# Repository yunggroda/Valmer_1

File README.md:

# Valmer_1

Custom split ergonomic keyboard project.

## Structure
- ergogen/ – layout and generation
- kicad/ – PCB design
- firmware/ – firmware (TBD)
- case/ – 3D printed parts
- docs/ – notes and decisions

## Status
Early development

## Goals
- Split keyboard
- RP2040 (Pro Micro)
- Ergogen-based workflow

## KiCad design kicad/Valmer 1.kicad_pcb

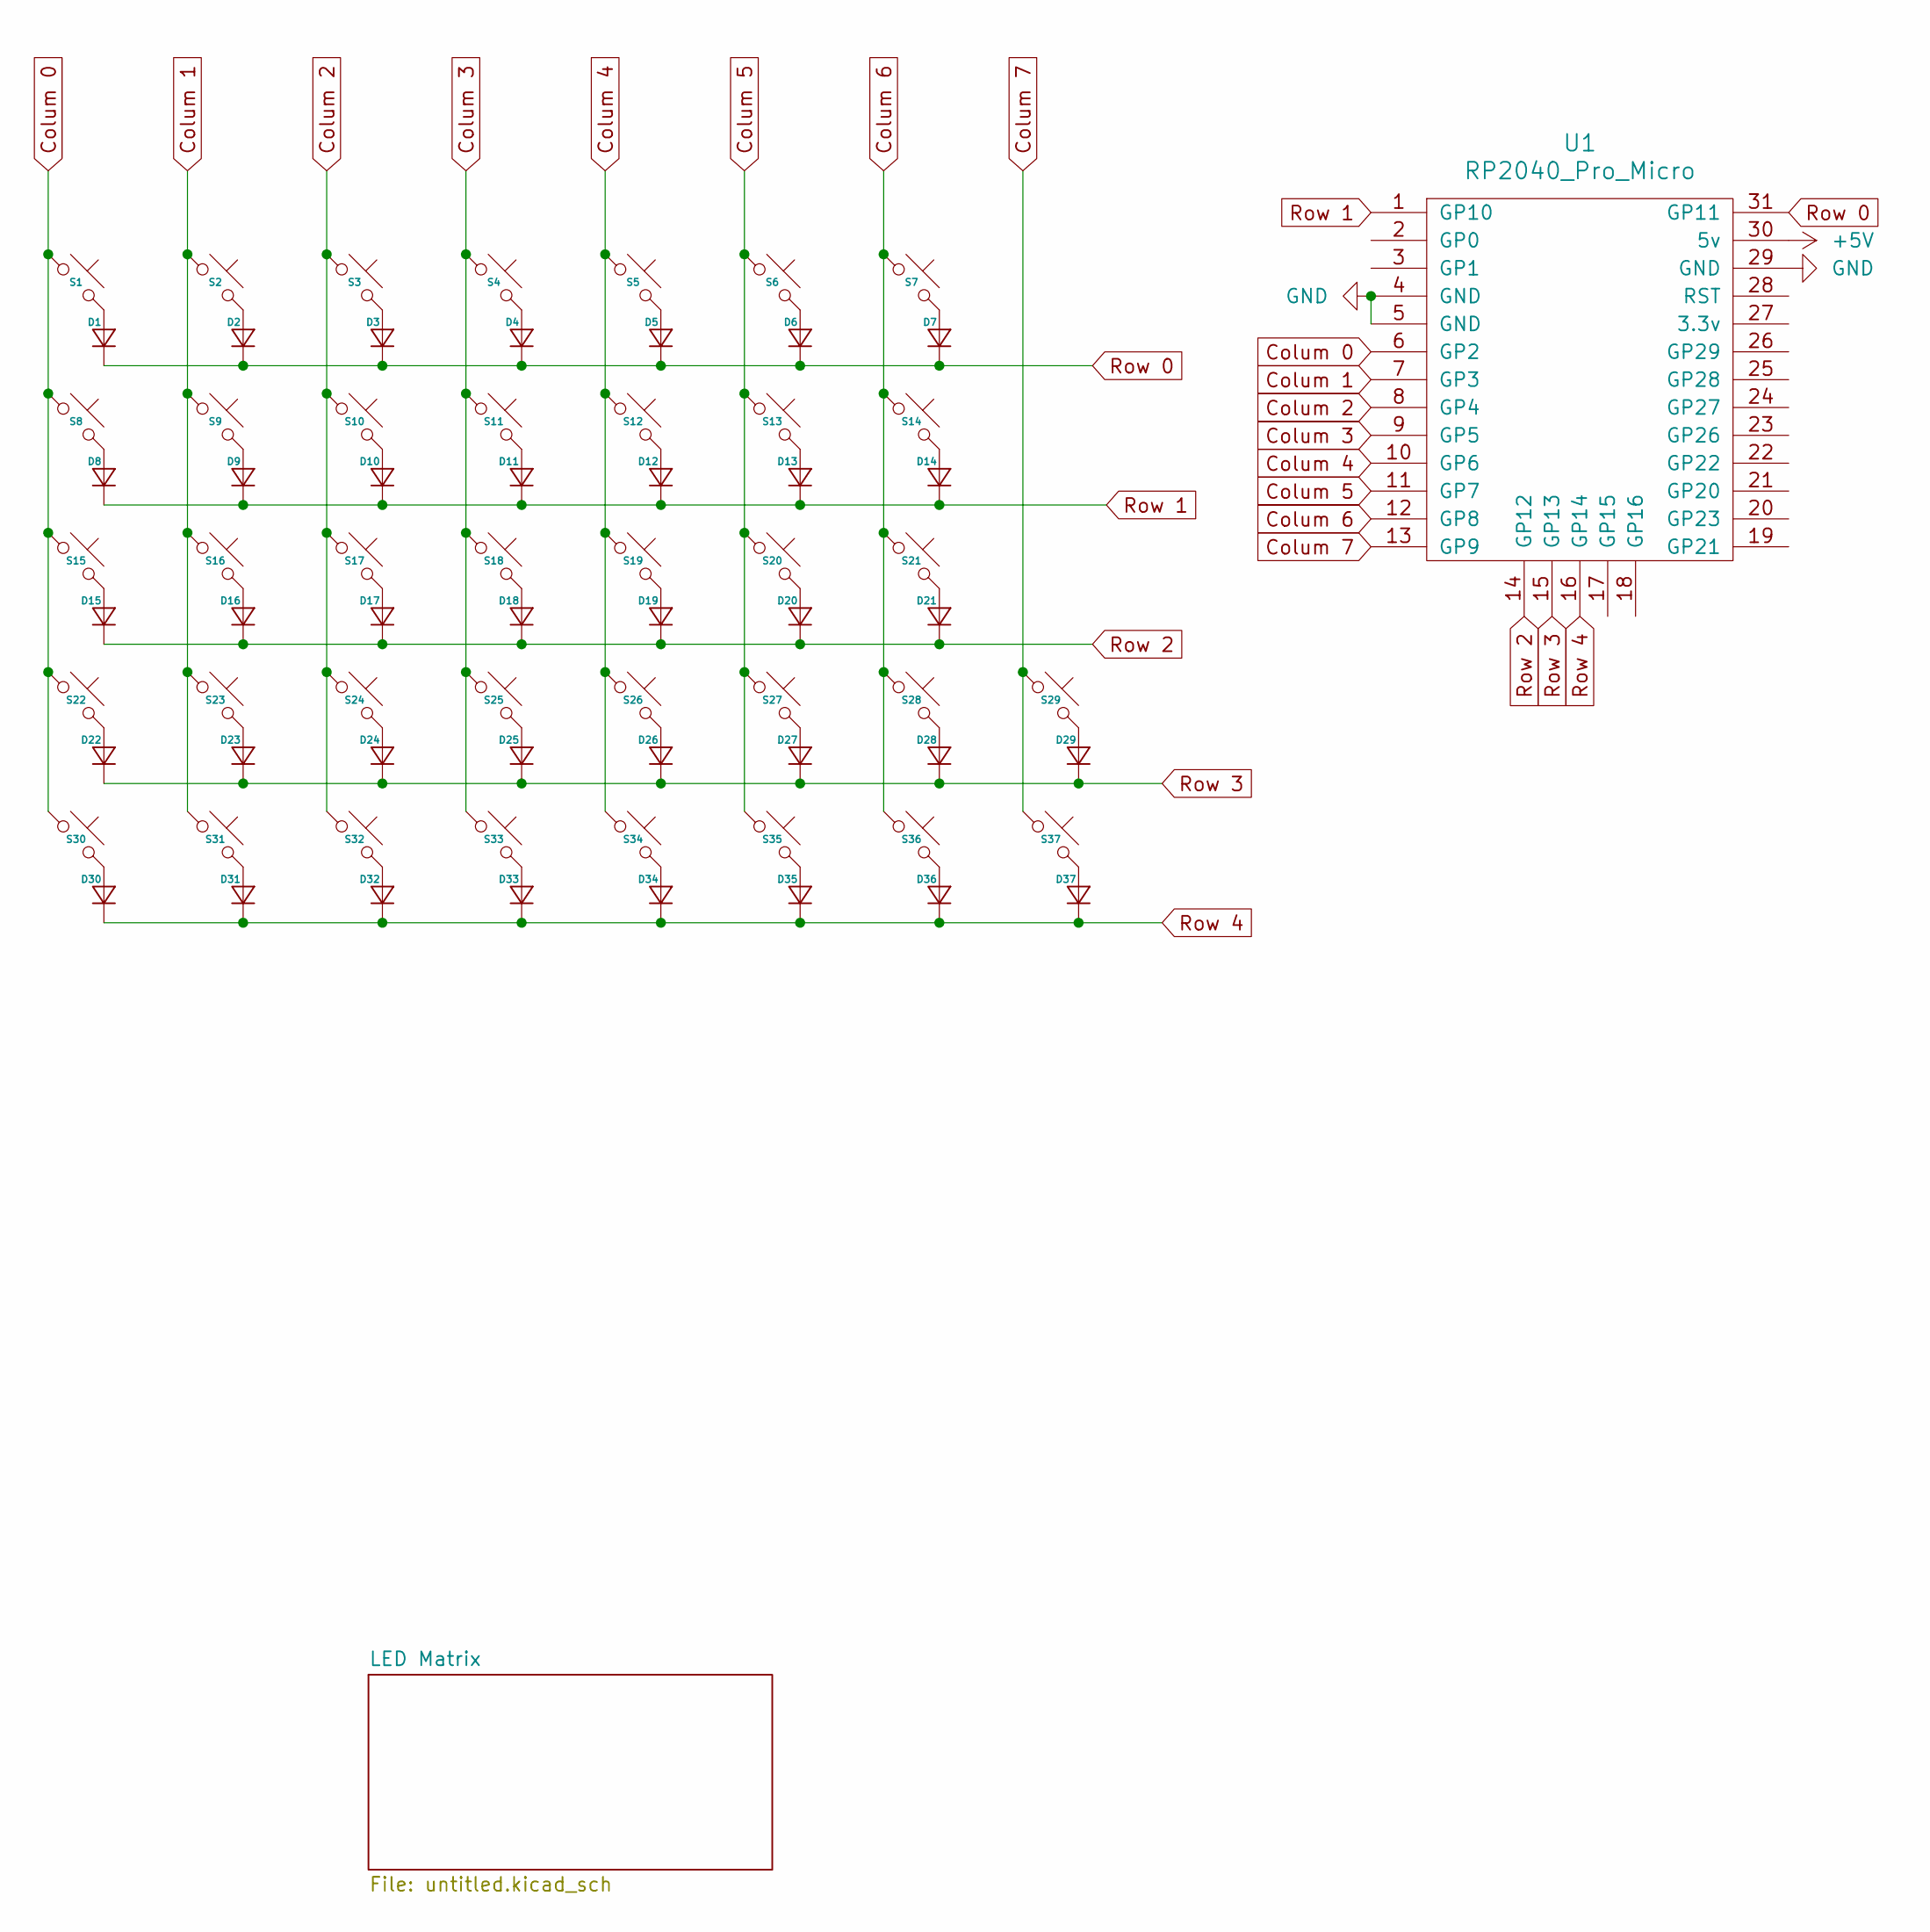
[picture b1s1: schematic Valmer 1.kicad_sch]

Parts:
D1, D2, D3, D4, D5, D6, D7, D8, D9, D10, D11, D12, D13, D14, D15, D16, D17, D18, D19, D20, D21, D22, D23, D24, D25, D26, D27, D28, D29, D30, D31, D32, D33, D34, D35, D36, D37: Diode_SOD-123
S1, S2, S3, S4, S5, S6, S7, S8, S9, S10, S11, S12, S13, S14, S15, S16, S17, S18, S19, S20, S21, S22, S23, S24, S25, S26, S27, S28, S29, S30, S31, S32, S33, S34, S35, S36, S37: Hotswap_Choc_V1V2_1.00u
U1: RP2040_Pro_Micro

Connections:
+5V: U1.30 (5v); also elsewhere on the board
Colum 0: S1.1, S8.1, S15.1, S22.1, S30.1, U1.6 (GP2)
Colum 1: S2.1, S9.1, S16.1, S23.1, S31.1, U1.7 (GP3)
Colum 2: S3.1, S10.1, S17.1, S24.1, S32.1, U1.8 (GP4)
Colum 3: S4.1, S11.1, S18.1, S25.1, S33.1, U1.9 (GP5)
Colum 4: S5.1, S12.1, S19.1, S26.1, S34.1, U1.10 (GP6)
Colum 5: S6.1, S13.1, S20.1, S27.1, S35.1, U1.11 (GP7)
Colum 6: S7.1, S14.1, S21.1, S28.1, S36.1, U1.12 (GP8)
Colum 7: S29.1, S37.1, U1.13 (GP9)
GND: U1.4 (GND), U1.5 (GND), U1.29 (GND); also elsewhere on the board
unnamed: D1.2 (A), S1.2
unnamed: D2.2 (A), S2.2
unnamed: D3.2 (A), S3.2
unnamed: D4.2 (A), S4.2
unnamed: D5.2 (A), S5.2
unnamed: D6.2 (A), S6.2
unnamed: D7.2 (A), S7.2
unnamed: D8.2 (A), S8.2
unnamed: D9.2 (A), S9.2
unnamed: D10.2 (A), S10.2
unnamed: D11.2 (A), S11.2
unnamed: D12.2 (A), S12.2
unnamed: D13.2 (A), S13.2
unnamed: D14.2 (A), S14.2
unnamed: D15.2 (A), S15.2
unnamed: D16.2 (A), S16.2
unnamed: D17.2 (A), S17.2
unnamed: D18.2 (A), S18.2
unnamed: D19.2 (A), S19.2
unnamed: D20.2 (A), S20.2
unnamed: D21.2 (A), S21.2
unnamed: D22.2 (A), S22.2
unnamed: D23.2 (A), S23.2
unnamed: D24.2 (A), S24.2
unnamed: D25.2 (A), S25.2
unnamed: D26.2 (A), S26.2
unnamed: D27.2 (A), S27.2
unnamed: D28.2 (A), S28.2
unnamed: D29.2 (A), S29.2
unnamed: D30.2 (A), S30.2
unnamed: D31.2 (A), S31.2
unnamed: D32.2 (A), S32.2
unnamed: D33.2 (A), S33.2
unnamed: D34.2 (A), S34.2
unnamed: D35.2 (A), S35.2
unnamed: D36.2 (A), S36.2
unnamed: D37.2 (A), S37.2
Row 0: D1.1 (K), D2.1 (K), D3.1 (K), D4.1 (K), D5.1 (K), D6.1 (K), D7.1 (K), U1.31 (GP11)
Row 1: D8.1 (K), D9.1 (K), D10.1 (K), D11.1 (K), D12.1 (K), D13.1 (K), D14.1 (K), U1.1 (GP10)
Row 2: D15.1 (K), D16.1 (K), D17.1 (K), D18.1 (K), D19.1 (K), D20.1 (K), D21.1 (K), U1.14 (GP12)
Row 3: D22.1 (K), D23.1 (K), D24.1 (K), D25.1 (K), D26.1 (K), D27.1 (K), D28.1 (K), D29.1 (K), U1.15 (GP13)
Row 4: D30.1 (K), D31.1 (K), D32.1 (K), D33.1 (K), D34.1 (K), D35.1 (K), D36.1 (K), D37.1 (K), U1.16 (GP14)

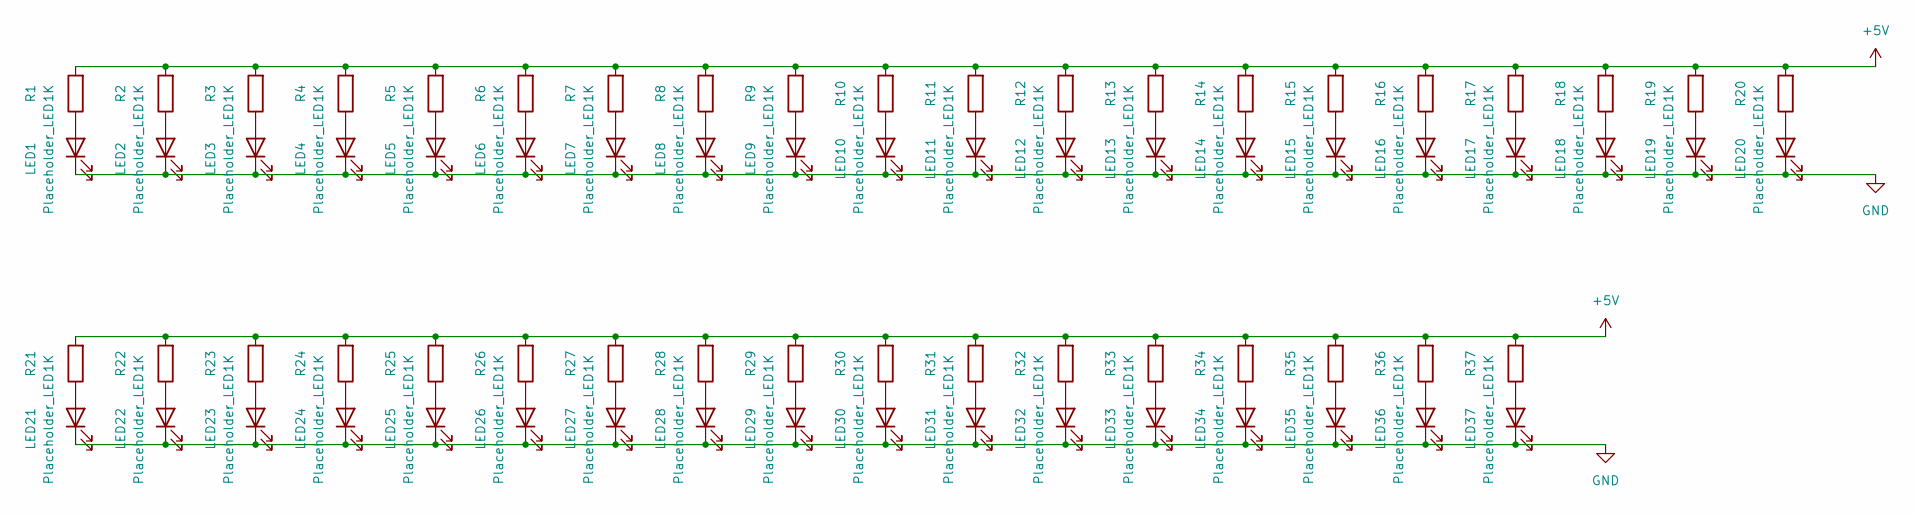
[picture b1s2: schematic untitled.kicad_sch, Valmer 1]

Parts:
LED1, LED2, LED3, LED4, LED5, LED6, LED7, LED8, LED9, LED10, LED11, LED12, LED13, LED14, LED15, LED16, LED17, LED18, LED19, LED20, LED21, LED22, LED23, LED24, LED25, LED26, LED27, LED28, LED29, LED30, LED31, LED32, LED33, LED34, LED35, LED36, LED37: Placeholder_LED; LED_0603_1608Metric
R1, R2, R3, R4, R5, R6, R7, R8, R9, R10, R11, R12, R13, R14, R15, R16, R17, R18, R19, R20, R21, R22, R23, R24, R25, R26, R27, R28, R29, R30, R31, R32, R33, R34, R35, R36, R37: 1K; R_0603_1608Metric

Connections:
+5V: R1.2, R2.2, R3.2, R4.2, R5.2, R6.2, R7.2, R8.2, R9.2, R10.2, R11.2, R12.2, R13.2, R14.2, R15.2, R16.2, R17.2, R18.2, R19.2, R20.2, R21.2, R22.2, R23.2, R24.2, R25.2, R26.2, R27.2, R28.2, R29.2, R30.2, R31.2, R32.2, R33.2, R34.2, R35.2, R36.2, R37.2; also elsewhere on the board
GND: LED1.1 (K), LED2.1 (K), LED3.1 (K), LED4.1 (K), LED5.1 (K), LED6.1 (K), LED7.1 (K), LED8.1 (K), LED9.1 (K), LED10.1 (K), LED11.1 (K), LED12.1 (K), LED13.1 (K), LED14.1 (K), LED15.1 (K), LED16.1 (K), LED17.1 (K), LED18.1 (K), LED19.1 (K), LED20.1 (K), LED21.1 (K), LED22.1 (K), LED23.1 (K), LED24.1 (K), LED25.1 (K), LED26.1 (K), LED27.1 (K), LED28.1 (K), LED29.1 (K), LED30.1 (K), LED31.1 (K), LED32.1 (K), LED33.1 (K), LED34.1 (K), LED35.1 (K), LED36.1 (K), LED37.1 (K); also elsewhere on the board
unnamed: LED1.2 (A), R1.1
unnamed: LED2.2 (A), R2.1
unnamed: LED3.2 (A), R3.1
unnamed: LED4.2 (A), R4.1
unnamed: LED5.2 (A), R5.1
unnamed: LED6.2 (A), R6.1
unnamed: LED7.2 (A), R7.1
unnamed: LED8.2 (A), R8.1
unnamed: LED9.2 (A), R9.1
unnamed: LED10.2 (A), R10.1
unnamed: LED11.2 (A), R11.1
unnamed: LED12.2 (A), R12.1
unnamed: LED13.2 (A), R13.1
unnamed: LED14.2 (A), R14.1
unnamed: LED15.2 (A), R15.1
unnamed: LED16.2 (A), R16.1
unnamed: LED17.2 (A), R17.1
unnamed: LED18.2 (A), R18.1
unnamed: LED19.2 (A), R19.1
unnamed: LED20.2 (A), R20.1
unnamed: LED21.2 (A), R21.1
unnamed: LED22.2 (A), R22.1
unnamed: LED23.2 (A), R23.1
unnamed: LED24.2 (A), R24.1
unnamed: LED25.2 (A), R25.1
unnamed: LED26.2 (A), R26.1
unnamed: LED27.2 (A), R27.1
unnamed: LED28.2 (A), R28.1
unnamed: LED29.2 (A), R29.1
unnamed: LED30.2 (A), R30.1
unnamed: LED31.2 (A), R31.1
unnamed: LED32.2 (A), R32.1
unnamed: LED33.2 (A), R33.1
unnamed: LED34.2 (A), R34.1
unnamed: LED35.2 (A), R35.1
unnamed: LED36.2 (A), R36.1
unnamed: LED37.2 (A), R37.1

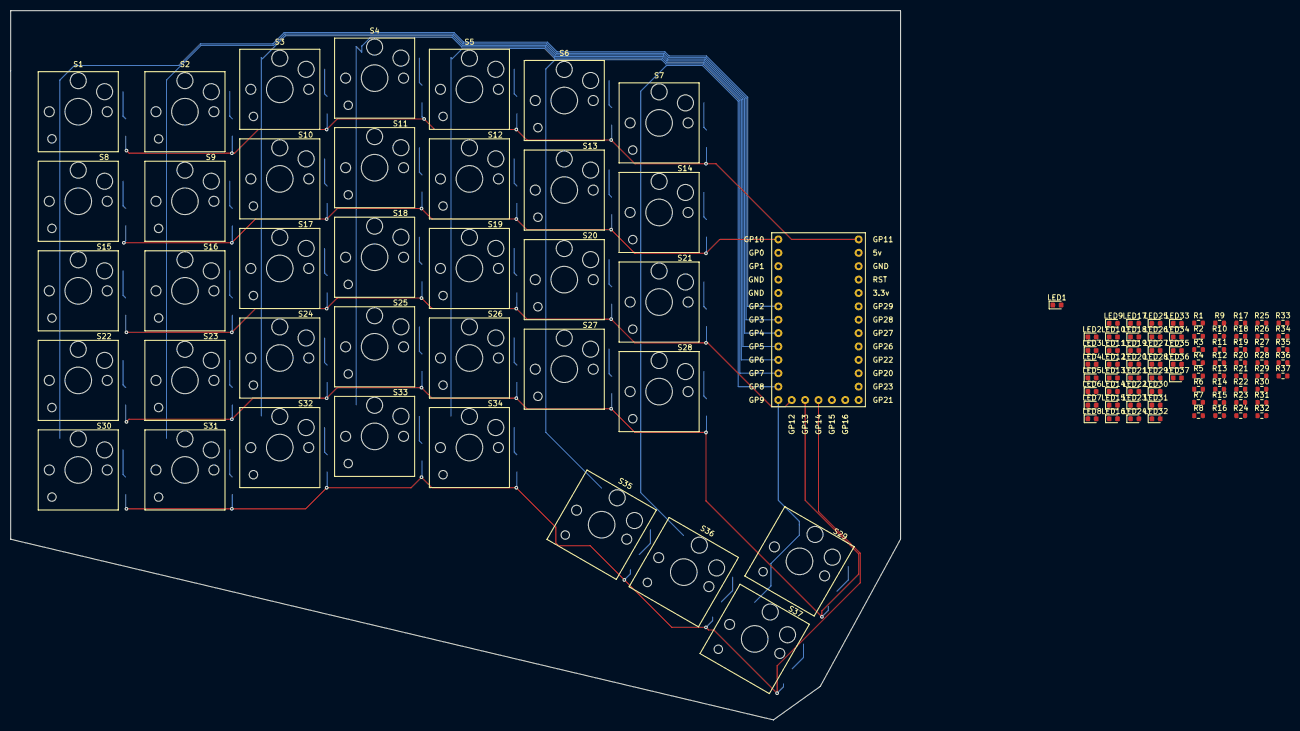
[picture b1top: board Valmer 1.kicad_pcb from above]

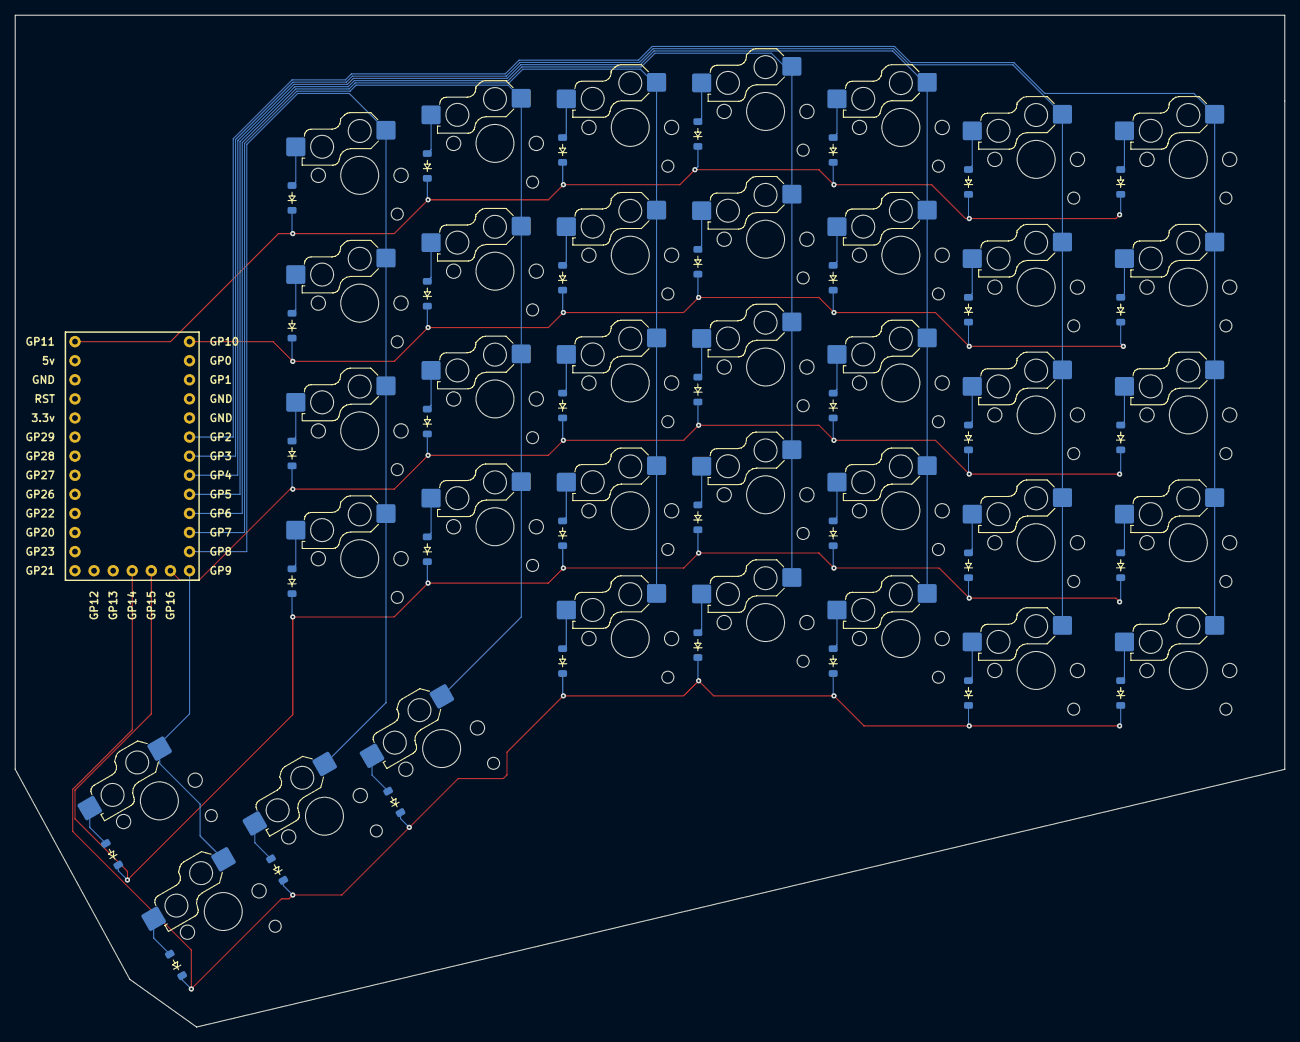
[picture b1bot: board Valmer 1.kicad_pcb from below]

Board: 4 copper layers, 168.9 x 134.6 mm, 149 parts (37 on the bottom side), 89 nets.

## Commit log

2026-03-21 Add project structure
2026-03-21 clean up
2026-03-21 add yaml valmer_1
2026-03-21 ergogen add
2026-03-22 kicad update
